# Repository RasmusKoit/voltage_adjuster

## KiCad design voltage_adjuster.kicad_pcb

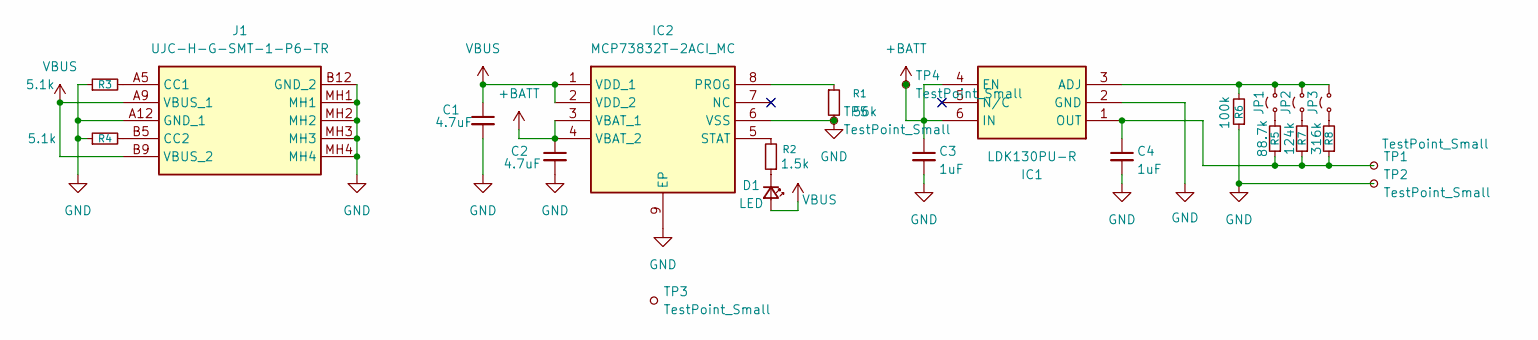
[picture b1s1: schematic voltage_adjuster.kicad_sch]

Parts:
C1, C2: 4.7uF; C_0603_1608Metric; Manufacturer Part Number LMK107BJ475KA-T; Mouser Part Number 963-LMK107BJ475KA-T
C3, C4: 1uF; C_0603_1608Metric; Manufacturer Part Number LMK107B7105KA-T; Mouser Part Number 963-LMK107B7105KA-T
D1: LED; LED_0603_1608Metric; Manufacturer Part Number LTST-C190KRKT; Mouser Part Number 859-LTST-C190KRKT
IC1: LDK130PU-R; LDK130PUR; Mouser Part Number 511-LDK130PU-R
IC2: MCP73832T-2ACI_MC; SON50P300X200X100-9N-D; Mouser Part Number 579-MCP73832T-2ACIMC
J1: UJC-H-G-SMT-1-P6-TR; UJCHGSMT1P6TR; Mouser Part Number 179-UJCHGSMTP6TR
JP1, JP2, JP3: Jumper_2_Small_Open; SolderJumper-2_P1.3mm_Open_RoundedPad1.0x1.5mm
R1: 56k; R_0603_1608Metric; Manufacturer Part Number CRG0603F56K; Mouser Part Number 279-CRG0603F56K
R2: 1.5k; R_0603_1608Metric; Manufacturer Part Number CRG0603F1K5; Mouser Part Number 279-CRG0603F1K5
R3, R4: 5.1k; R_0603_1608Metric; Manufacturer Part Number CRG0603F5K1; Mouser Part Number 279-CRG0603F5K1
R5: 88.7k; R_0603_1608Metric; Manufacturer Part Number RC0603FR-0788K7L; Mouser Part Number 603-RC0603FR-0788K7L
R6: 100k; R_0603_1608Metric; Manufacturer Part Number RCA0603100KFKEC; Mouser Part Number 71-RCA0603100KFKEC
R7: 124k; R_0603_1608Metric; Manufacturer Part Number AC0603FR-07124KL; Mouser Part Number 603-AC0603FR-07124KL
R8: 316k; R_0603_1608Metric; Manufacturer Part Number AC0603FR-07316KL; Mouser Part Number 603-AC0603FR-07316KL
TP1, TP2, TP4, TP5: TestPoint_Small; TestPoint_Pad_D1.0mm
TP3: TestPoint_Small; Salt-8x8

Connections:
+BATT: C2.1, C3.1, IC1.4 (EN), IC1.6 (IN), IC2.3 (VBAT_1), IC2.4 (VBAT_2), TP4.1
GND: C1.2, C2.2, C3.2, C4.2, IC1.2 (GND), IC2.6 (VSS), IC2.9 (EP), J1.A12 (GND_1), J1.B12 (GND_2), J1.MH1, J1.MH2, J1.MH3, J1.MH4, R1.2, R3.1, R4.1, R6.1, TP2.1, TP5.1
unnamed: D1.1 (K), R2.1
unnamed: IC1.3 (ADJ), JP1.2 (B), JP2.2 (B), JP3.2 (B), R6.2
unnamed: C4.1, IC1.1 (OUT), R5.1, R7.1, R8.1, TP1.1
unnamed: IC2.8 (PROG), R1.1
unnamed: IC2.5 (STAT), R2.2
unnamed: J1.A5 (CC1), R3.2
unnamed: J1.B5 (CC2), R4.2
unnamed: JP1.1 (A), R5.2
unnamed: JP2.1 (A), R7.2
unnamed: JP3.1 (A), R8.2
VBUS: C1.1, D1.2 (A), IC2.1 (VDD_1), IC2.2 (VDD_2), J1.A9 (VBUS_1), J1.B9 (VBUS_2)

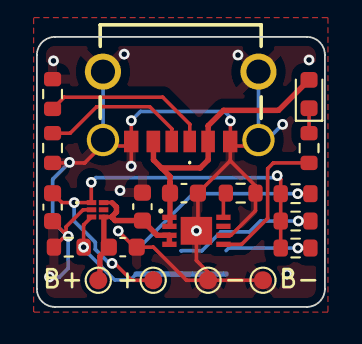
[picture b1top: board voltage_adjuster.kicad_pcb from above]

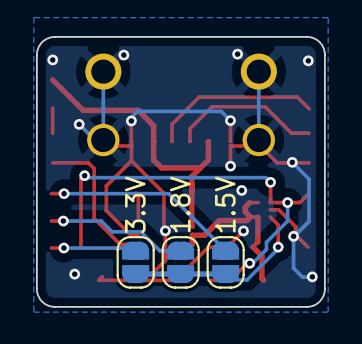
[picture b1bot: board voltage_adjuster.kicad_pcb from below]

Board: 2 copper layers, 16.0 x 15.0 mm, 24 parts (4 on the bottom side), 13 nets.

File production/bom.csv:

Designator,Footprint,Quantity,Value,LCSC Part #
"C1, C2",0603,2,4.7uF,
"C3, C4",0603,2,1uF,
D1,0603,1,LED,
IC1,LDK130PUR,1,LDK130PU-R,
IC2,SON50P300X200X100-9N-D,1,MCP73832T-2ACI_MC,
J1,UJCHGSMT1P6TR,1,UJC-H-G-SMT-1-P6-TR,
"JP1, JP2, JP3",SolderJumper-2_P1.3mm_Open_RoundedPad1.0x1.5mm,3,Jumper_2_Small_Open,
R1,0603,1,56k,
R2,0603,1,1.5k,
"R3, R4",0603,2,5.1k,
R5,0603,1,88.7k,
R6,0603,1,100k,
R7,0603,1,124k,
R8,0603,1,316k,
"TP1, TP2, TP4, TP5",TestPoint_Pad_D1.0mm,4,TestPoint_Small,
TP3,Salt-8x8,1,TestPoint_Small,

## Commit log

2026-05-12 move the usb-c a bit
2026-05-12 changed the size to be more uniform
2026-05-12 adjusted pcb size
2026-06-01 random changes
2026-06-02 add step file for the model
2026-06-18 generate html bom
2026-06-25 fixed bom
